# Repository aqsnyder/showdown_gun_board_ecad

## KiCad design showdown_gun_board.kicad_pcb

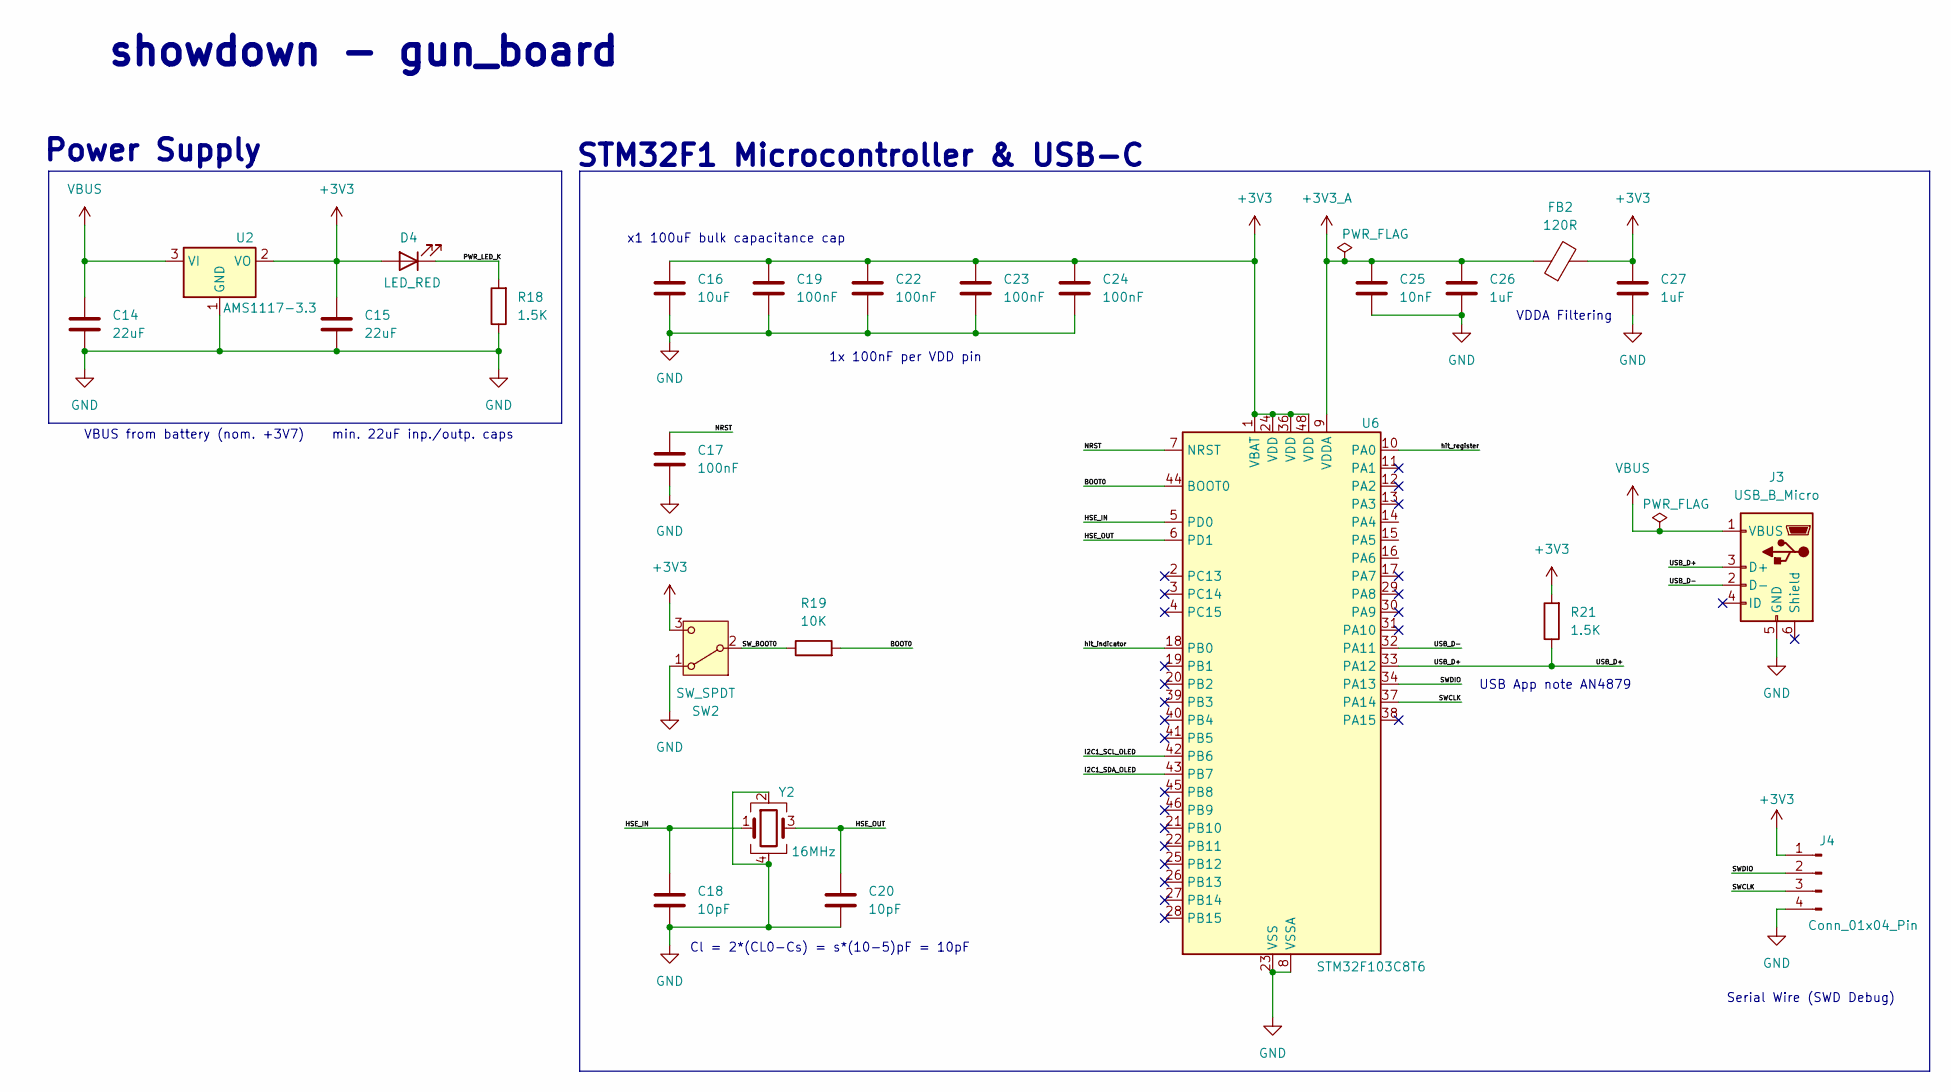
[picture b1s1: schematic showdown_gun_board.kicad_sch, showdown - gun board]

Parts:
C14, C15: 22uF; C_0603_1608Metric
C16: 10uF; C_0603_1608Metric
C17, C19, C22, C23, C24: 100nF; C_0603_1608Metric
C18, C20: 10pF; C_0603_1608Metric
C25: 10nF; C_0603_1608Metric
C26, C27: 1uF; C_0603_1608Metric
D4: LED_RED; LED_0805_2012Metric
FB2: 120R; L_0603_1608Metric
J3: USB_B_Micro; USB_Micro-AB_Molex_47590-0001
J4: Conn_01x04_Pin; PinHeader_1x04_P2.54mm_Horizontal
R18, R21: 1.5K; R_0603_1608Metric
R19: 10K; R_0603_1608Metric
SW2: SW_SPDT; SW_Slide-03_Wuerth-WS-SLTV_10x2.5x6.4_P2.54mm
U2: AMS1117-3.3; SOT-223-3_TabPin2
U6: STM32F103C8T6; LQFP-48_7x7mm_P0.5mm
Y2: 16MHz; Crystal_SMD_3225-4Pin_3.2x2.5mm

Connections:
+3V3: C15.1, C16.1, C19.1, C22.1, C23.1, C24.1, C27.1, D4.2 (A), FB2.2, J4.1, R21.2, SW2.3 (C), U2.2 (VO), U6.1 (VBAT), U6.24 (VDD), U6.36 (VDD), U6.48 (VDD)
+3V3_A: C25.1, C26.1, FB2.1, U6.9 (VDDA)
/BOOT0: R19.2, U6.44 (BOOT0)
/HSE_IN: C18.1, U6.5 (PD0), Y2.1
/HSE_OUT: C20.1, U6.6 (PD1), Y2.3
/I2C1_SCL_OLED: U6.42 (PB6)
/I2C1_SDA_OLED: U6.43 (PB7)
/NRST: C17.1, U6.7 (NRST)
/PWR_LED_K: D4.1 (K), R18.2
/SWCLK: J4.3, U6.37 (PA14)
/SWDIO: J4.2, U6.34 (PA13)
/SW_BOOT0: R19.1, SW2.2 (B)
/USB_D+: J3.3 (D+), R21.1, U6.33 (PA12)
/USB_D-: J3.2 (D-), U6.32 (PA11)
/hit_indicator: U6.18 (PB0)
/hit_register: U6.10 (PA0)
GND: C14.2, C15.2, C16.2, C17.2, C18.2, C19.2, C20.2, C22.2, C23.2, C24.2, C25.2, C26.2, C27.2, J3.5 (GND), J4.4, R18.1, SW2.1 (A), U2.1 (GND), U6.8 (VSSA), U6.23 (VSS), U6.35 (VSS), U6.47 (VSS), Y2.2, Y2.4
VBUS: C14.1, J3.1 (VBUS), U2.3 (VI)

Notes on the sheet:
x1 100uF bulk capacitance cap
Power Supply
1x 100nF per VDD pin
STM32F1 Microcontroller & USB-C
Cl = 2*(CL0-Cs) = s*(10-5)pF = 10pF
VBUS from battery (nom. +3V7) min. 22uF inp./outp. caps
VDDA Filtering
USB App note AN4879
showdown - gun_board
Serial Wire (SWD Debug)

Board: 2 copper layers, 24 parts (0 on the bottom side), 14 nets, no tracks yet.

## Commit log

2024-10-17 init commit
2024-10-18 null
